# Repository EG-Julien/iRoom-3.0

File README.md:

# iRoom 3.0
My goal is to create a fully voice controlled house. Nowaday that kind of systems are really expensive and you have to change multiple devices. I don't want to replace anything just modify what's existing and create a complete new world.

## Follow me

 => [Kariboo.cc](//www.kariboo.cc)

## How ?
I have to create a voice to text (and text to voice) system. Since I'm not a 500 engineers team I had to lookup to the market something that do this for me. After something like 10 minutes, I found the Google Home Mini which is perfect for I have to do. It's compatible with IFTT, some Homebridge package exist to control any Google Home object from Siri (Yes I have an iPhone ...).
Now the next step was the music. I love music. I just can't work without any music ! That's why I started my project from this point. Create a voice controlled HiFi systems.

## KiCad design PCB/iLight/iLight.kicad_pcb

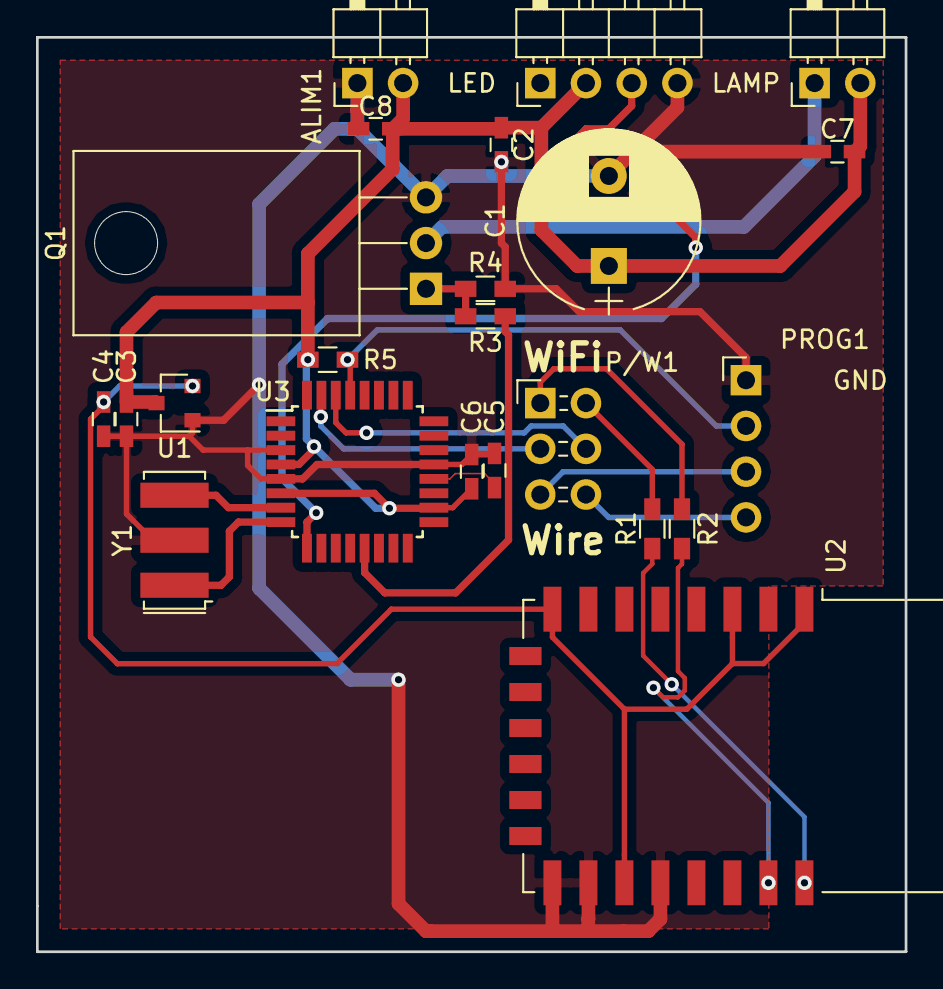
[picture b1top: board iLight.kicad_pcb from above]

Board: 2 copper layers, 48.3 x 50.8 mm, 23 parts (0 on the bottom side), 19 nets.

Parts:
ALIM1: Conn_01x02_Female; Pin_Header_Angled_1x02_Pitch2.54mm
C1: 10µF; CP_Radial_D10.0mm_P5.00mm
C2, C3, C4, C5, C6, C7, C8: 100nF; C_0603_HandSoldering
LAMP: LAMP; Pin_Header_Angled_1x02_Pitch2.54mm
LED: LED; Pin_Header_Angled_1x04_Pitch2.54mm
P/W1: Conn_02x03_Odd_Even_Shielded; Pin_Header_Angled_2x03_Pitch2.54mm
PROG1: Conn_01x04_Female; Pin_Header_Angled_1x04_Pitch2.54mm
Q1: IRLB8721PBF; TO-220-3_Horizontal
R1, R2: 4.7k; R_0603_HandSoldering
R3, R5: 10k; R_0603_HandSoldering
R4: 100k; R_0603_HandSoldering
U1: LT1117-3.3; SOT-23
U2: ESP-12F; ESP-12E
U3: ATmega328-AU; TQFP-32_7x7mm_Pitch0.8mm
Y1: Resonator; Resonator_SMD-3pin_7.2x3.0mm

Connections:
+5V: ALIM1.2, C1.1, C2.1, C3.2, C6.2, C7.2, C8.2, LAMP.2, LED.2, R5.1, U1.3, U3.4, U3.6, U3.18
/RST: PROG1.2, R5.2, U3.29
/RX: P/W1.4, U3.30
/RXP: P/W1.6, PROG1.4
/RXW: P/W1.2, R1.2
/TX: P/W1.3, U3.31
/TXP: P/W1.5, PROG1.3
/TXW: P/W1.1, R2.1
DATA: LED.3, U3.9
GNDD: ALIM1.1, C1.2, C2.2, C3.1, C4.1, C5.2, C6.1, C7.1, C8.1, LED.4, PROG1.1, Q1.3, R4.2, U1.1, U2.15, U2.16, U2.18, U3.3, U3.5, U3.21, Y1.2
unnamed: C4.2, U1.2, U2.1, U2.3, U2.8, U2.17
unnamed: C5.1, U3.20
unnamed: LAMP.1, Q1.2
unnamed: Q1.1, R3.2, R4.1
unnamed: R1.1, U2.22
unnamed: R2.2, U2.21
unnamed: R3.1, U3.13
unnamed: U3.7, Y1.3
unnamed: U3.8, Y1.1

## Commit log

2018-11-23 Base of the application
2018-11-23 Ajout fonction lumière
2018-11-23 Modification live
2018-12-09 Changement de la récupération des commandes
2018-12-09 HotFix Script Python
2018-12-22 Mise a jour vaec allumage de l'ordi
2019-03-23 [FIXED] = Fixed an error on database
2019-03-24 HOT FIX 1
2019-03-24 Fixed double calls
2019-03-31 Ajout dun script python de test + client&server wifi
2019-03-31 HOT FIX
2019-03-31 MAJ Wifi
2019-03-31 Modification d'instructions
2019-04-06 Ajout de iDesk.ino
2019-04-07 Added PCB - Updated Readme.md
